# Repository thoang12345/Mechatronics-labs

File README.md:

This is for my bum ahh mechatronics class

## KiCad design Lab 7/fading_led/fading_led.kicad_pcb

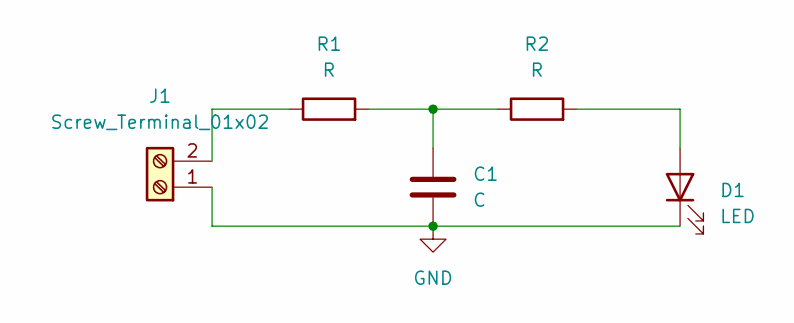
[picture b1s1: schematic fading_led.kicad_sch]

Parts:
C1: C; CP_Elec_8x10
D1: LED; LED_D3.0mm
J1: Screw_Terminal_01x02; TerminalBlock_Phoenix_MKDS-1,5-2-5.08_1x02_P5.08mm_Horizont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
R1, R2: R; R_1812_4532Metric

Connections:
GND: C1.2, D1.1 (K), J1.1
unnamed: C1.1, R1.2, R2.1
unnamed: D1.2 (A), R2.2
unnamed: J1.2, R1.1

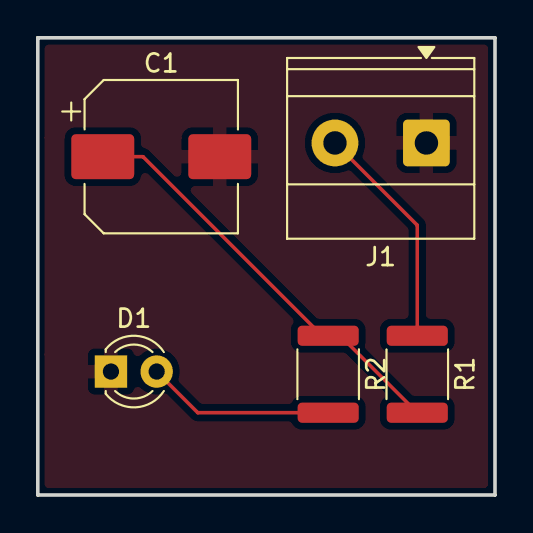
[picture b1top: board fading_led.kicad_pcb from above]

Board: 2 copper layers, 25.4 x 25.4 mm, 5 parts (0 on the bottom side), 4 nets.
